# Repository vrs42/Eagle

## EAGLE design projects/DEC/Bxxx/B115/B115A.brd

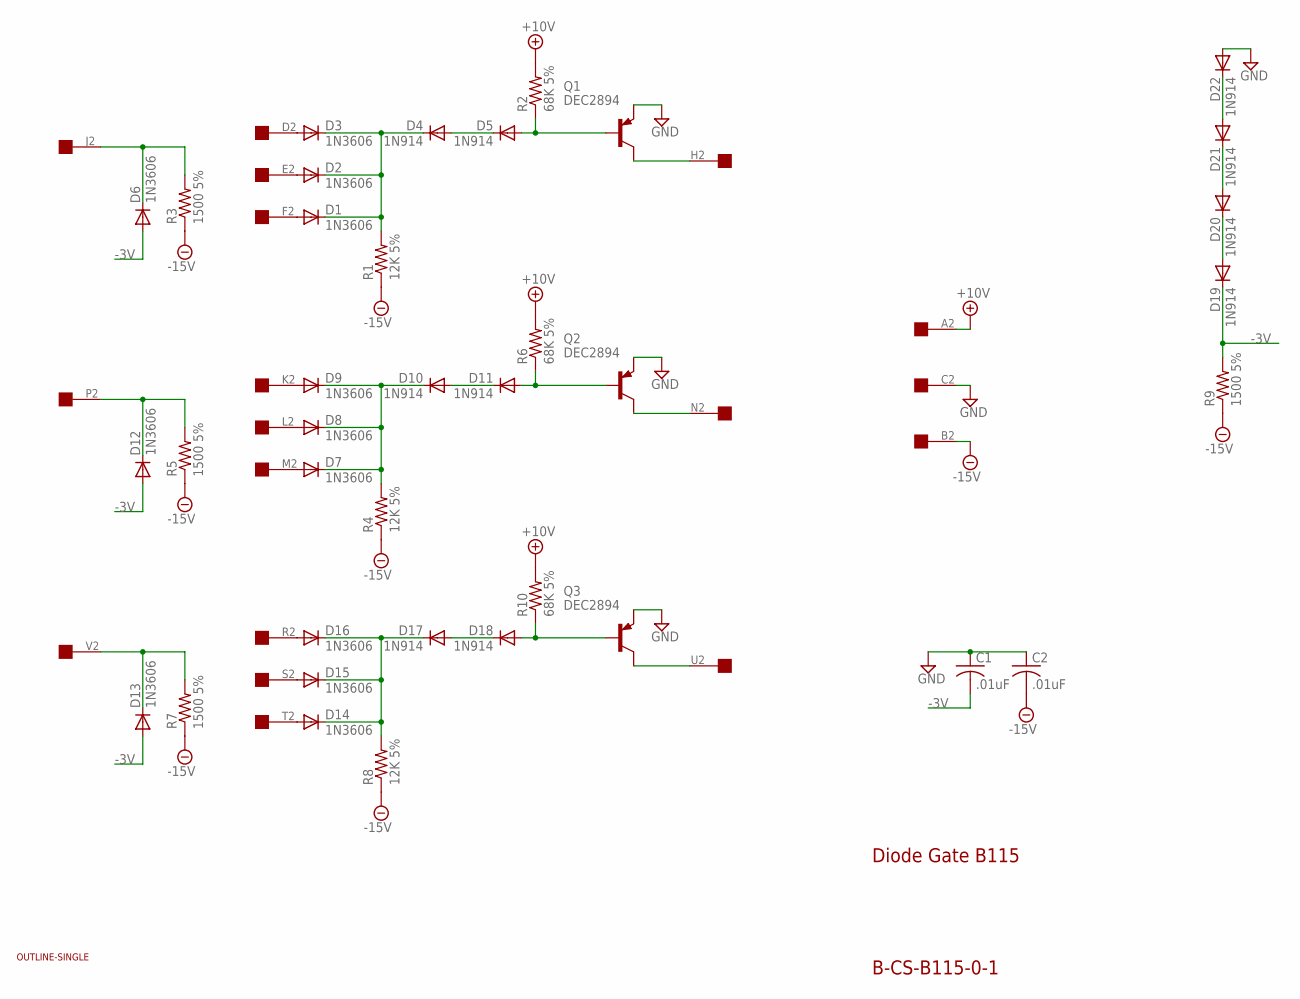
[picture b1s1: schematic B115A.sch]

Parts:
C1, C2: .01uF; C050-025X075
D1, D2, D3, D6, D7, D8, D9, D12, D13, D14, D15, D16: 1N3606; DO35-10
D4, D5, D10, D11, D17, D18, D19, D20, D21, D22: 1N914; DO35-10
Q1, Q2, Q3: DEC2894; TO39
R1, R4, R8: 12K 5%; 0207/10
R2, R6, R10: 68K 5%; 0207/10
R3, R5, R7, R9: 1500 5%; 0207/10
U$1: OUTLINE-SINGLE; SINGLE
U$2: EDGE-1; EDGE-CON1

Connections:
+10V: R2.2, R6.2, R10.2, U$2.A2
-3V: C1.2, D6.A, D12.A, D13.A, D19.C, R9.2
-15V: C2.2, R1.1, R3.1, R4.1, R5.1, R7.1, R8.1, R9.1, U$2.B2
GND: C1.1, C2.1, D22.A, Q1.1 (E), Q2.1 (E), Q3.1 (E), U$2.C2
unnamed: D7.C, D8.C, D9.C, D10.C, R4.2
unnamed: D1.A, U$2.F2
unnamed: D5.A, Q1.2 (B), R2.1
unnamed: D2.A, U$2.E2
unnamed: D1.C, D2.C, D3.C, D4.C, R1.2
unnamed: D9.A, U$2.K2
unnamed: D8.A, U$2.L2
unnamed: D7.A, U$2.M2
unnamed: D10.A, D11.C
unnamed: D3.A, U$2.D2
unnamed: Q1.3 (C), U$2.H2
unnamed: D11.A, Q2.2 (B), R6.1
unnamed: Q2.3 (C), U$2.N2
unnamed: D14.C, D15.C, D16.C, D17.C, R8.2
unnamed: D4.A, D5.C
unnamed: D16.A, U$2.R2
unnamed: D6.C, R3.2, U$2.J2
unnamed: D15.A, U$2.S2
unnamed: D14.A, U$2.T2
unnamed: D12.C, R5.2, U$2.P2
unnamed: D17.A, D18.C
unnamed: D18.A, Q3.2 (B), R10.1
unnamed: Q3.3 (C), U$2.U2
unnamed: D13.C, R7.2, U$2.V2
unnamed: D21.A, D22.C
unnamed: D20.A, D21.C
unnamed: D19.A, D20.C

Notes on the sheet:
Diode Gate B115
B-CS-B115-0-1

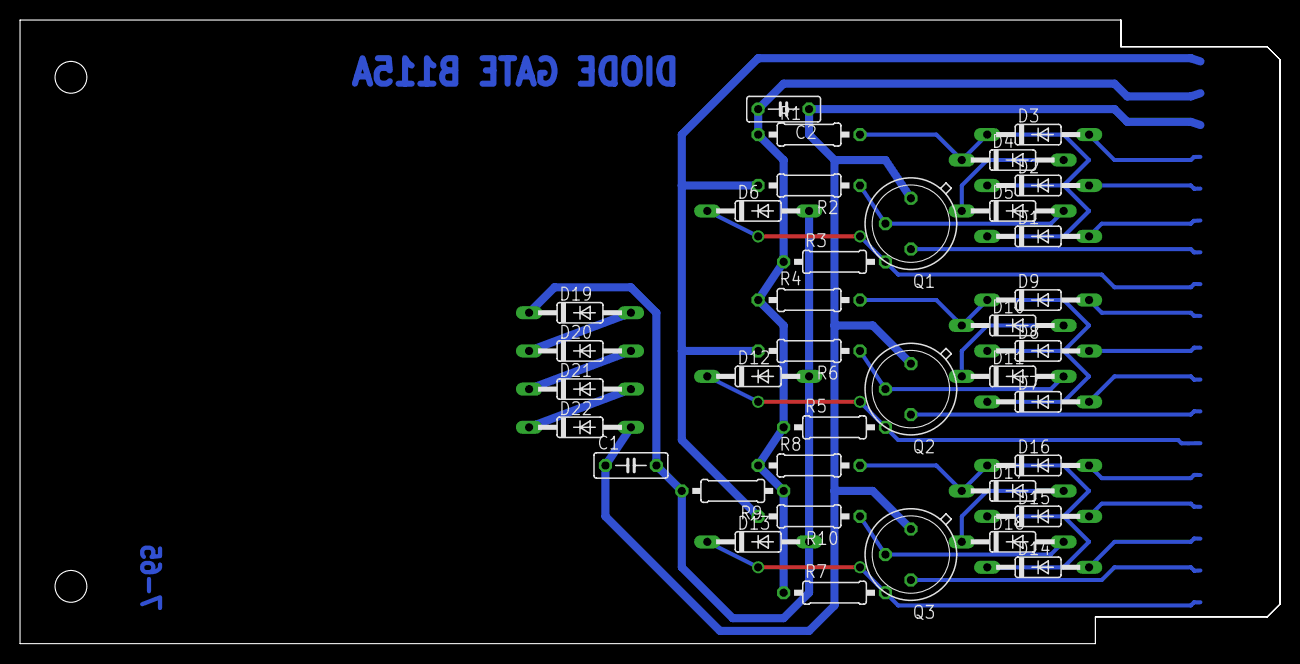
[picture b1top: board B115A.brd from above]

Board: 2 copper layers, 125.7 x 62.2 mm, 39 parts (0 on the bottom side), 31 nets.

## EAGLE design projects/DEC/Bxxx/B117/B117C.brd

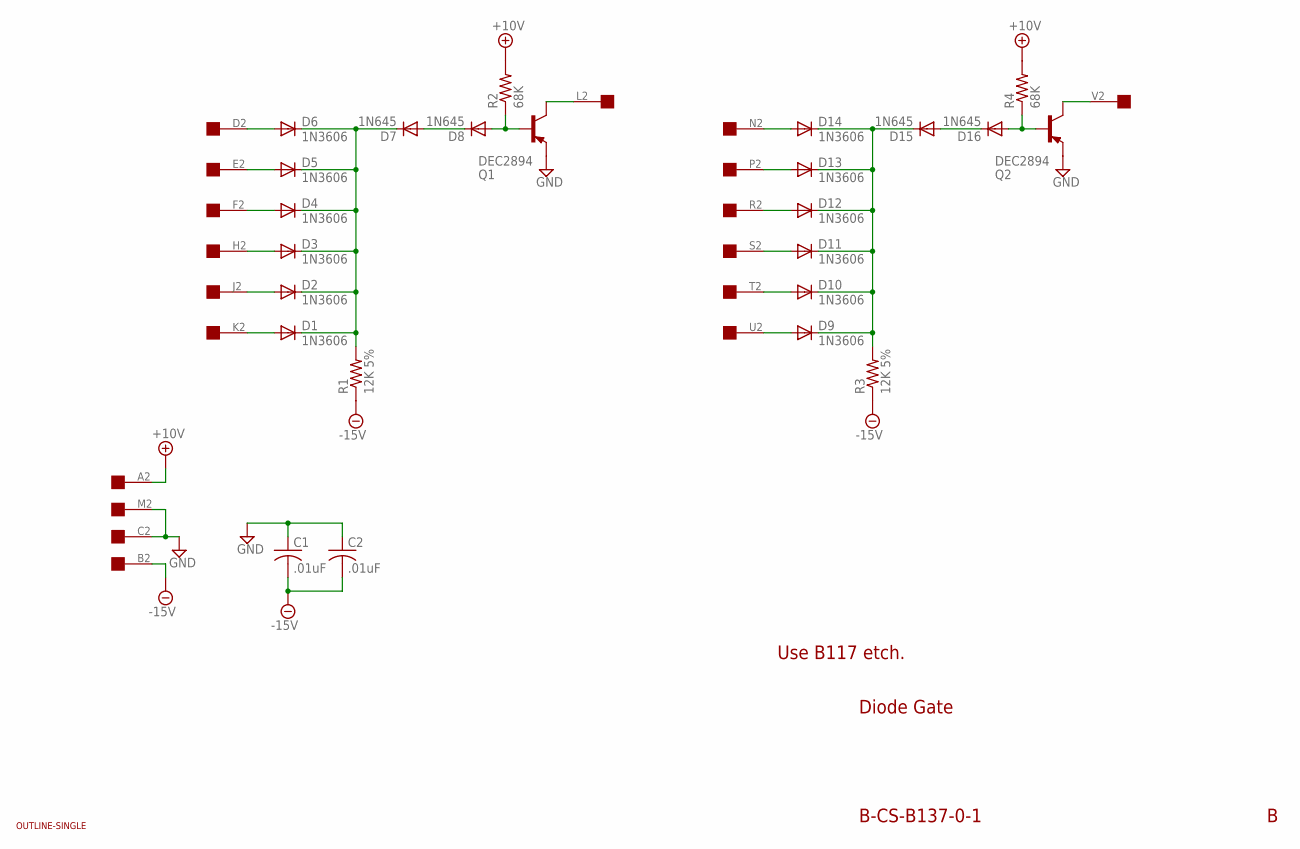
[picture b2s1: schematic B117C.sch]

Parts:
C1, C2: .01uF; C050-025X075
D1, D2, D3, D4, D5, D6, D9, D10, D11, D12, D13, D14: 1N3606; DO35-10
D7, D8, D15, D16: 1N645; DO35-10
Q1, Q2: DEC2894; TO5
R1, R3: 12K 5%; 0207/10
R2, R4: 68K; 0207/10
U$1: OUTLINE-SINGLE; SINGLE
U$2: EDGE-1; EDGE-CON1

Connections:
+10V: R2.2, R4.2, U$2.A2
-15V: C1.2, C2.2, R1.1, R3.1, U$2.B2
D: D6.A, U$2.D2
E: D5.A, U$2.E2
F: D4.A, U$2.F2
GND: C1.1, C2.1, Q1.1 (E), Q2.1 (E), U$2.C2, U$2.M2
H: D3.A, U$2.H2
J: D2.A, U$2.J2
K: D1.A, U$2.K2
L: Q1.3 (C), U$2.L2
N: D14.A, U$2.N2
unnamed: D1.C, D2.C, D3.C, D4.C, D5.C, D6.C, D7.C, R1.2
unnamed: D7.A, D8.C
unnamed: D8.A, Q1.2 (B), R2.1
unnamed: D9.C, D10.C, D11.C, D12.C, D13.C, D14.C, D15.C, R3.2
unnamed: D15.A, D16.C
unnamed: D16.A, Q2.2 (B), R4.1
P: D13.A, U$2.P2
R: D12.A, U$2.R2
S: D11.A, U$2.S2
T: D10.A, U$2.T2
U: D9.A, U$2.U2
V: Q2.3 (C), U$2.V2

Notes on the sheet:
Diode Gate
B-CS-B137-0-1
Use B117 etch.

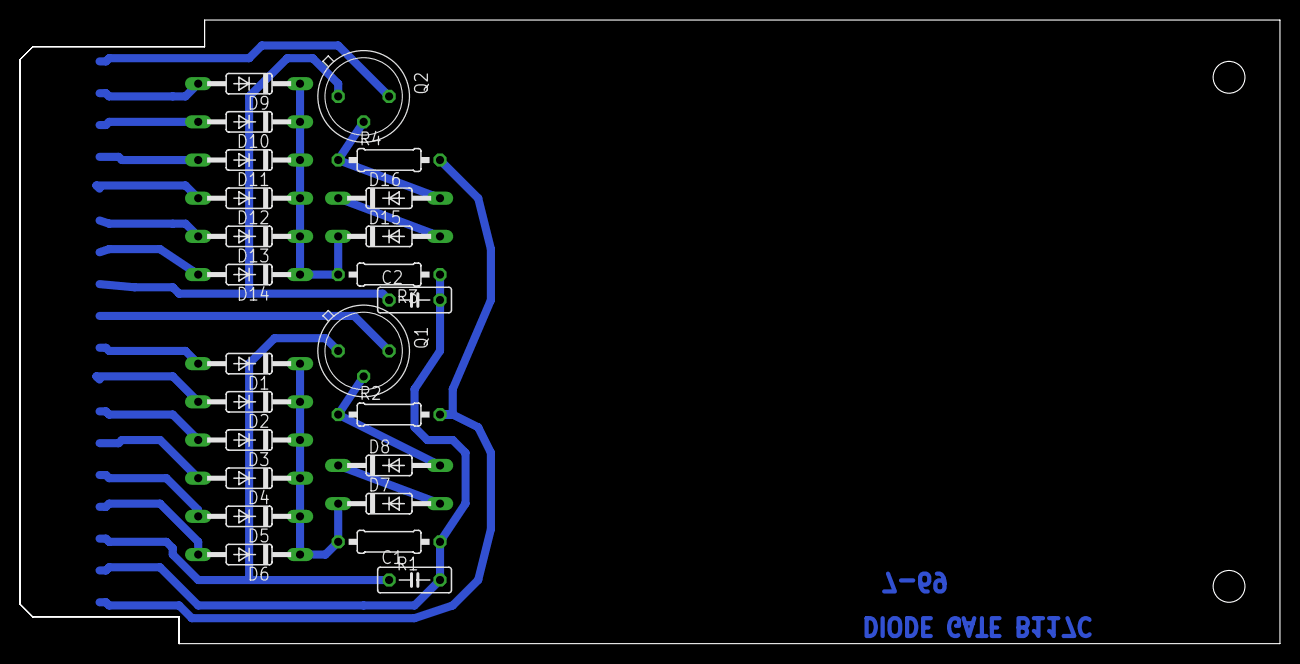
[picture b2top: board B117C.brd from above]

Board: 2 copper layers, 125.7 x 62.2 mm, 26 parts (0 on the bottom side), 23 nets.

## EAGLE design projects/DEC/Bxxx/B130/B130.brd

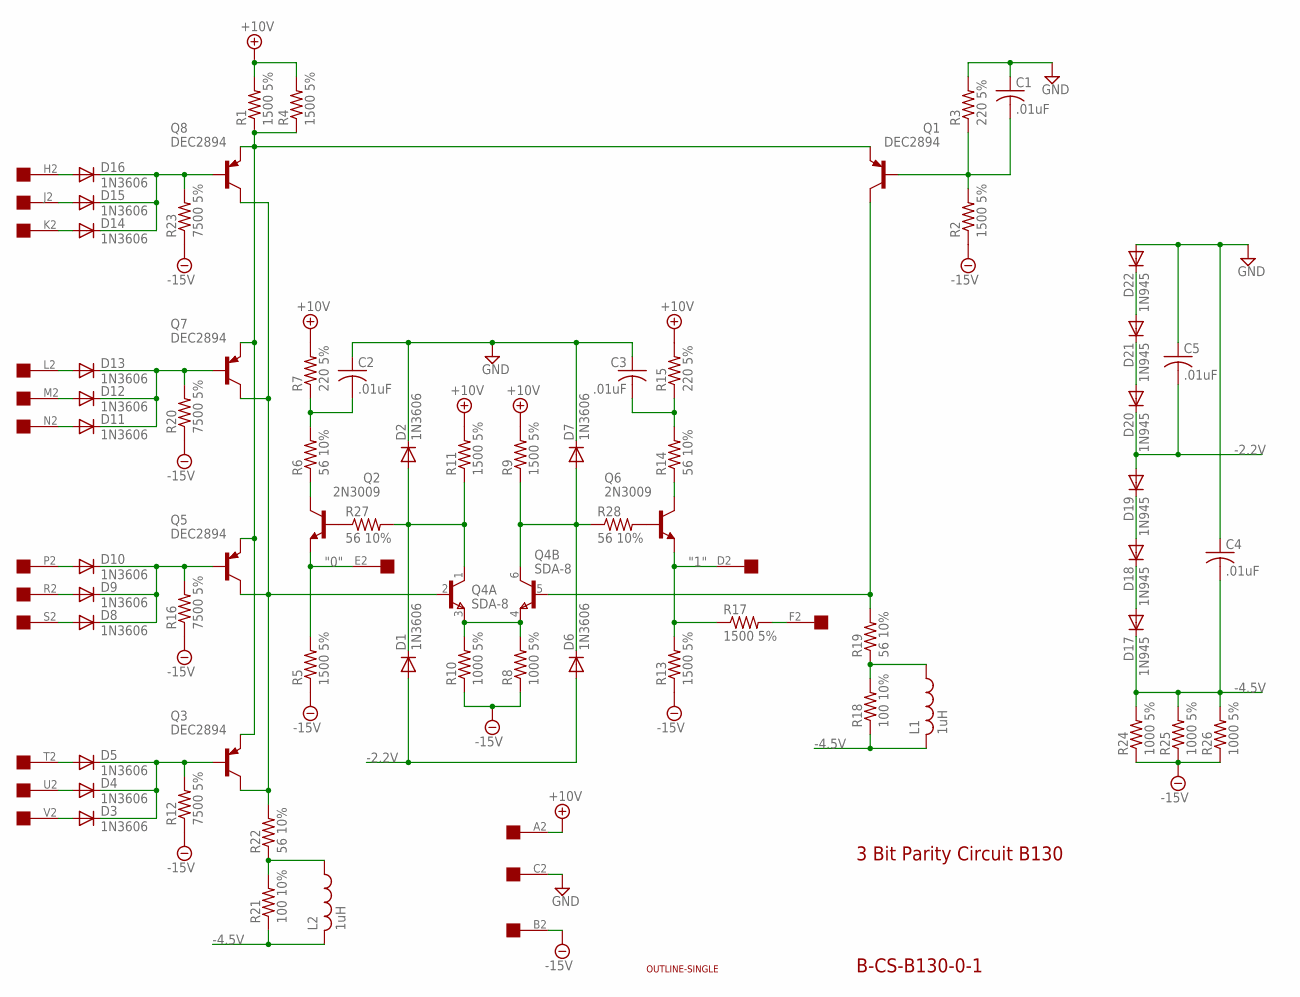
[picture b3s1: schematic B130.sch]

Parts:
C1, C2, C3, C4, C5: .01uF; C050-025X075
D1, D2, D3, D4, D5, D6, D7, D8, D9, D10, D11, D12, D13, D14, D15, D16: 1N3606; DO35-10
D17, D18, D19, D20, D21, D22: 1N945; DO35-10
L1, L2: 1uH; 0207/10
Q1, Q3, Q5, Q7, Q8: DEC2894; TO39
Q2, Q6: 2N3009; TO5
Q4: SDA-8; TO78
R1, R2, R4, R5, R9, R11, R13, R17: 1500 5%; 0207/10
R3, R7, R15: 220 5%; 0207/10
R6, R14, R19, R22, R27, R28: 56 10%; 0207/10
R8, R10, R24, R25, R26: 1000 5%; 0207/10
R12, R16, R20, R23: 7500 5%; 0207/10
R18, R21: 100 10%; 0207/10
U$1: OUTLINE-SINGLE; SINGLE
U$2: EDGE-1; EDGE-CON1

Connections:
"0": Q2.1 (E), R5.2, U$2.E2
"1": Q6.1 (E), R13.2, R17.1, U$2.D2
+10V: R1.2, R4.2, R7.2, R9.2, R11.2, R15.2, U$2.A2
-2.2V: C5.2, D1.A, D6.A, D19.A, D20.C
-4.5V: C4.2, D17.C, L1.2, L2.2, R18.1, R21.1, R24.2, R25.2, R26.2
-15V: R2.1, R5.1, R8.1, R10.1, R12.1, R13.1, R16.1, R20.1, R23.1, R24.1, R25.1, R26.1, U$2.B2
GND: C1.1, C2.1, C3.1, C4.1, C5.1, D2.C, D7.C, D22.A, R3.2, U$2.C2
unnamed: D16.A, U$2.H2
unnamed: D18.A, D19.C
unnamed: D15.A, U$2.J2
unnamed: D17.A, D18.C
unnamed: Q1.1 (E), Q3.1 (E), Q5.1 (E), Q7.1 (E), Q8.1 (E), R1.1, R4.1
unnamed: D14.A, U$2.K2
unnamed: D14.C, D15.C, D16.C, Q8.2 (B), R23.2
unnamed: D13.A, U$2.L2
unnamed: D12.A, U$2.M2
unnamed: L2.1, R21.2, R22.1
unnamed: D11.A, U$2.N2
unnamed: D11.C, D12.C, D13.C, Q7.2 (B), R20.2
unnamed: D10.A, U$2.P2
unnamed: D9.A, U$2.R2
unnamed: D8.A, U$2.S2
unnamed: D8.C, D9.C, D10.C, Q5.2 (B), R16.2
unnamed: D5.A, U$2.T2
unnamed: D4.A, U$2.U2
unnamed: D3.A, U$2.V2
unnamed: D3.C, D4.C, D5.C, Q3.2 (B), R12.2
unnamed: Q3.3 (C), Q4.2 (B), Q5.3 (C), Q7.3 (C), Q8.3 (C), R22.2
unnamed: Q4.3 (E), Q4.4 (E), R8.2, R10.2
unnamed: D1.C, D2.A, Q4.1 (C), R11.1, R27.2
unnamed: D6.C, D7.A, Q4.6 (C), R9.1, R28.1
unnamed: Q2.2 (B), R27.1
unnamed: D21.A, D22.C
unnamed: D20.A, D21.C
unnamed: Q6.2 (B), R28.2
unnamed: Q1.3 (C), Q4.5 (B), R19.2
unnamed: C1.2, Q1.2 (B), R2.2, R3.1
unnamed: R17.2, U$2.F2
unnamed: Q6.3 (C), R14.1
unnamed: Q2.3 (C), R6.1
unnamed: C2.2, R6.2, R7.1
unnamed: C3.2, R14.2, R15.1
unnamed: L1.1, R18.2, R19.1

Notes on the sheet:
3 Bit Parity Circuit B130
B-CS-B130-0-1

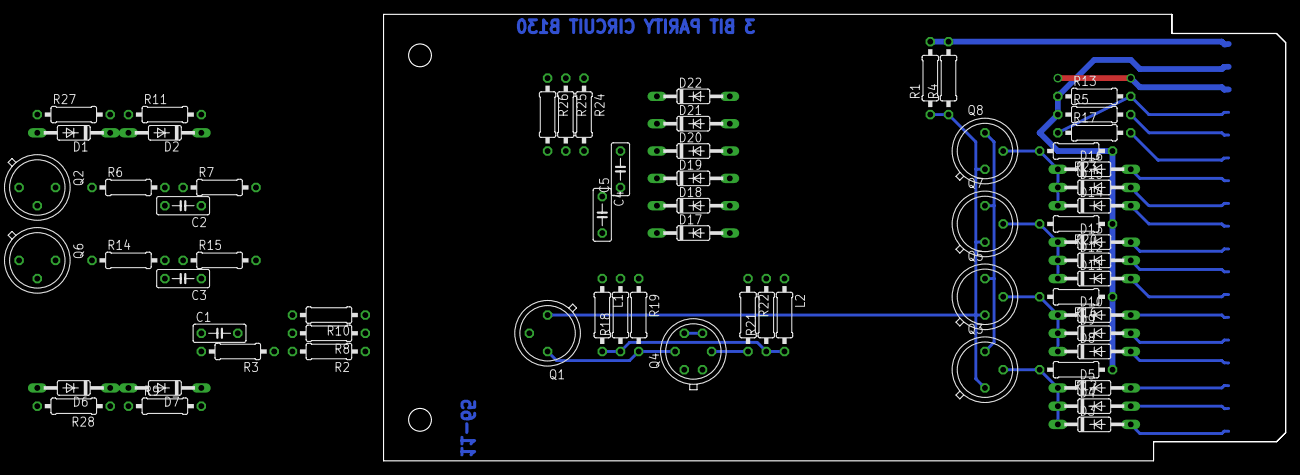
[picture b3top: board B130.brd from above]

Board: 2 copper layers, 125.7 x 62.2 mm, 67 parts (0 on the bottom side), 43 nets.
